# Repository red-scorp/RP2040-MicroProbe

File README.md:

```
 ___   ___  ___   ___     _   ___                          
| |_) | |_)  ) ) / / \ /_| | / / \                         
|_| \ |_|   /_/_ \_\_/   |_| \_\_/                         
 _      _   __    ___   ___   ___   ___   ___   ___   ____ 
| |\/| | | / /`  | |_) / / \ | |_) | |_) / / \ | |_) | |_  
|_|  | |_| \_\_, |_| \ \_\_/ |_|   |_| \ \_\_/ |_|_) |_|__ 
```

# RP2040-MicroProbe Project

The **RP2040-MicroProbe** project aims to create smaller version of RP2040-DebugProbe.

## RP2040-MicroProbe Board

The **RP2040-MicroProbe** board is a 4-layer design intended to accommodate the popular Raspberry Pi RP2040 MCU with all required component to function identically to Raspberry Pi Debug Probe.

This board features target JTAG connector and PC host micro-USB connector. It also has a SWD connector and UART connector for the main MCU debugging. The board is pin-compatible with Raspberry Pi Debug Probe and can be used with the same picoprobe SW.

Preview:

You can view the [Schematics in PDF format](doc/RP2040-MicroProbe.pdf) for detailed information.

STEP 3D file is available [with pins](doc/RP2040-MicroProbe.step).

Features:

- Very small form-factor of about 40x18mm.
- Raspberry Pi RP2040 MCU as a heart of the board.
- 2x5 1.27mm JTAG connector for programming and debugging.
- 1x8 2.54mm SWD/UART/Power connector for programming and debugging.
- Micro USB connector for power and communication.
- Several LEDs to indicate power and status.
- Castellated holes connector for main MCU debugging.
- BOOTSEL button to enter the bootloader mode for flashing new picoprobe SW.
- Pin-compatible with Raspberry Pi Debug Probe.
- Extra TARGET_RESET line connected to GPIO10 for target MCU reset over JTAG.
- Flat bottom side for easy mounting as a daughter board.

CAM files, as well as the BOM and CPL files for JLCPCB, are available.

## Version History

### v1.0b1

Initial release for testing purposes.

## Links

- [Raspberry Pi RP2040 information page](https://www.raspberrypi.com/documentation/microcontrollers/rp2040.html).
- [Raspberry Pi Debug Probe information page](https://www.raspberrypi.com/documentation/microcontrollers/debug-probe.html).
- [Picoprobe SW for the board](https://github.com/raspberrypi/picoprobe).

## How to Help

Your contributions as code, resources, or finances are welcome! Please contact me directly via email at andriy.golovnya@gmail.com or through my [GitHub profile](https://github.com/red-scorp).

If you'd like to make a financial contribution, you can donate via [PayPal](http://paypal.me/redscorp) or [Ko-Fi](http://ko-fi.com/redscorp). Your support is greatly appreciated.

Thanks in advance!

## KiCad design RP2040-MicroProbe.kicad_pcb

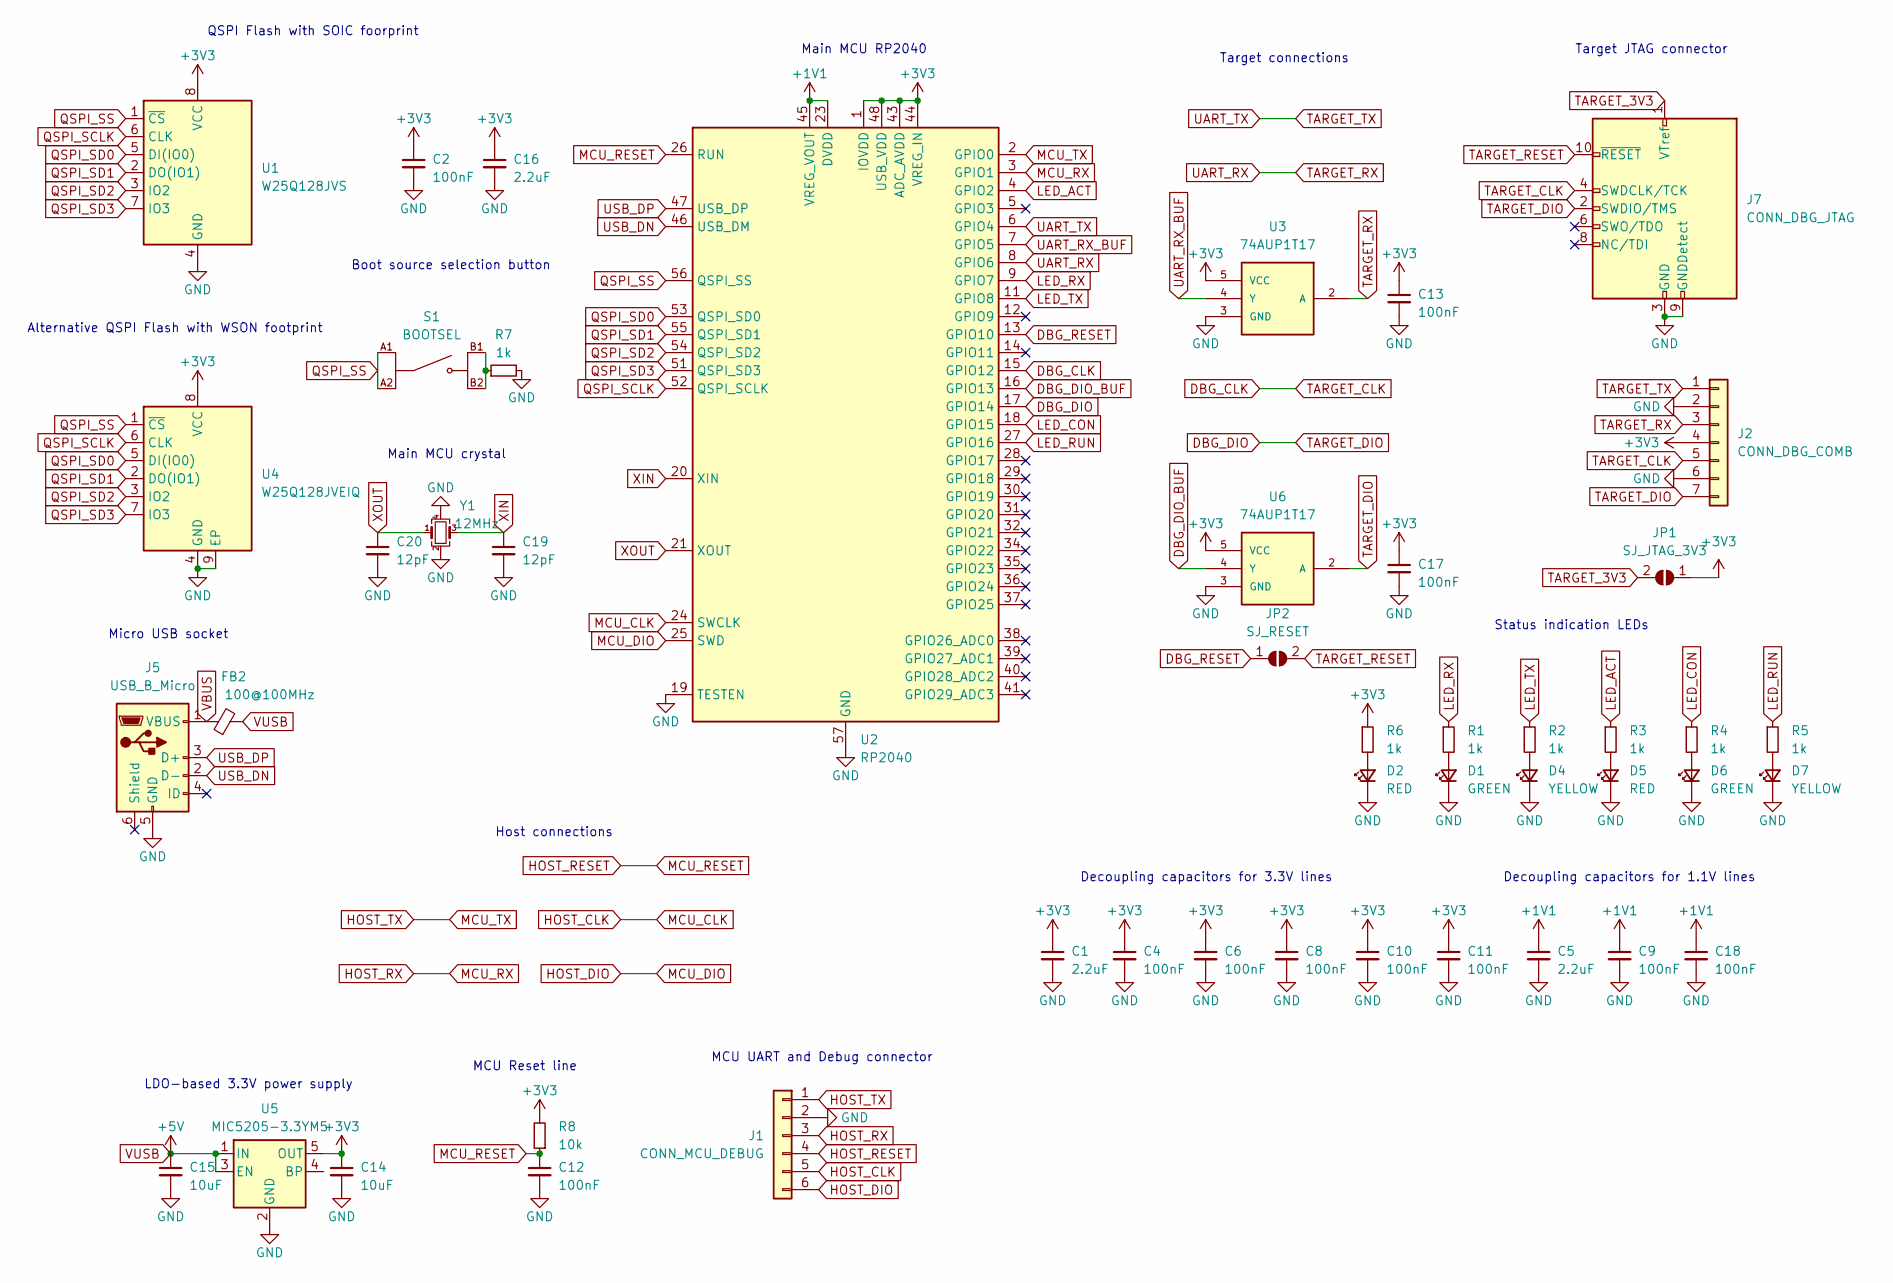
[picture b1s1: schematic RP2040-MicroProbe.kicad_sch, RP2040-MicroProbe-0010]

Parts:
C1, C5, C16: 2.2uF; C_0603_1608Metric
C2, C4, C6, C8, C9, C10, C11, C12, C13, C17, C18: 100nF; C_0402_1005Metric
C14, C15: 10uF; C_0805_2012Metric
C19, C20: 12pF; C_0402_1005Metric
D1, D6: GREEN; LED_0603_1608Metric
D2, D5: RED; LED_0603_1608Metric
D4, D7: YELLOW; LED_0603_1608Metric
FB2: 100@100MHz; L_0805_2012Metric
J1: CONN_MCU_DEBUG; PinHeader_1x06_P2.54mm_Vertical
J2: CONN_DBG_COMB; PinSocket_1x07_P2.54mm_Vertical
J5: USB_B_Micro; USB_Micro-B_Molex_47346-0001
J7: CONN_DBG_JTAG; PinHeader_2x05_P1.27mm_Vertical_SMD
JP1: SJ_JTAG_3V3; SolderJumper-2_P1.3mm_Open_TrianglePad1.0x1.5mm
JP2: SJ_RESET; SolderJumper-2_P1.3mm_Open_TrianglePad1.0x1.5mm
R1, R2, R3, R4, R5, R6, R7: 1k; R_0402_1005Metric
R8: 10k; R_0402_1005Metric
S1: BOOTSEL; SW_EVPBB0AAB000; DIGI-KEY_PART_NUMBER P19888CT-ND
U1: W25Q128JVS; SOIC-8_5.23x5.23mm_P1.27mm
U2: RP2040; QFN-56-1EP_7x7mm_P0.4mm_EP3.2x3.2mm
U3, U6: 74AUP1T17; SOT-353_SC-70-5
U4: W25Q128JVEIQ; WSON-8-1EP_6x5mm_P1.27mm_EP3.4x4.3mm
U5: MIC5205-3.3YM5; SOT-23-5
Y1: 12MHz; Crystal_SMD_3225-4Pin_3.2x2.5mm

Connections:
+1V1: C5.1, C9.1, C18.1, U2.23 (DVDD), U2.45 (VREG_VOUT), U2.50 (DVDD)
+3V3: C1.1, C2.1, C4.1, C6.1, C8.1, C10.1, C11.1, C13.1, C14.1, C16.1, C17.1, J2.4, JP1.1 (A), R6.1, R8.2, U1.8 (VCC), U2.1 (IOVDD), U2.10 (IOVDD), U2.22 (IOVDD), U2.33 (IOVDD), U2.42 (IOVDD), U2.43 (ADC_AVDD), U2.44 (VREG_IN), U2.48 (USB_VDD), U2.49 (IOVDD), U3.5 (VCC), U4.8 (VCC), U5.5 (OUT), U6.5 (VCC)
DBG_CLK: J2.5, J7.4 (SWDCLK/TCK), U2.15 (GPIO12)
DBG_DIO: J2.7, J7.2 (SWDIO/TMS), U2.17 (GPIO14), U6.2 (A)
DBG_DIO_BUF: U2.16 (GPIO13), U6.4 (Y)
DBG_RESET: JP2.1 (A), U2.13 (GPIO10)
GND: C1.2, C2.2, C4.2, C5.2, C6.2, C8.2, C9.2, C10.2, C11.2, C12.2, C13.2, C14.2, C15.2, C16.2, C17.2, C18.2, C19.2, C20.2, D1.1 (K), D2.1 (K), D4.1 (K), D5.1 (K), D6.1 (K), D7.1 (K), J1.2, J2.2, J2.6, J5.5 (GND), J7.3 (GND), J7.5 (GND), J7.9 (GNDDetect), R7.2, U1.4 (GND), U2.19 (TESTEN), U2.57 (GND), U3.3 (GND), U4.4 (GND), U4.9 (EP), U5.2 (GND), U6.3 (GND), Y1.2, Y1.4
HOST_CLK: J1.5, U2.24 (SWCLK)
HOST_DIO: J1.6, U2.25 (SWD)
HOST_RESET: C12.1, J1.4, R8.1, U2.26 (RUN)
HOST_RX: J1.3, U2.3 (GPIO1)
HOST_TX: J1.1, U2.2 (GPIO0)
LED_ACT: R3.1, U2.4 (GPIO2)
LED_CON: R4.1, U2.18 (GPIO15)
LED_RUN: R5.1, U2.27 (GPIO16)
LED_RX: R1.1, U2.9 (GPIO7)
LED_TX: R2.1, U2.11 (GPIO8)
unnamed: D1.2 (A), R1.2
unnamed: D2.2 (A), R6.2
unnamed: D4.2 (A), R2.2
unnamed: D5.2 (A), R3.2
unnamed: D6.2 (A), R4.2
unnamed: D7.2 (A), R5.2
unnamed: R7.1, S1.B1, S1.B2
QSPI_SCLK: U1.6 (CLK), U2.52 (QSPI_SCLK), U4.6 (CLK)
QSPI_SD0: U1.5 (DI(IO0)), U2.53 (QSPI_SD0), U4.5 (DI(IO0))
QSPI_SD1: U1.2 (DO(IO1)), U2.55 (QSPI_SD1), U4.2 (DO(IO1))
QSPI_SD2: U1.3 (IO2), U2.54 (QSPI_SD2), U4.3 (IO2)
QSPI_SD3: U1.7 (IO3), U2.51 (QSPI_SD3), U4.7 (IO3)
QSPI_SS: S1.A1, S1.A2, U1.1 (~CS), U2.56 (QSPI_SS), U4.1 (~CS)
TARGET_3V3: J7.1 (VTref), JP1.2 (B)
TARGET_RESET: J7.10 (~RESET), JP2.2 (B)
TARGET_RX: J2.3, U2.8 (GPIO6), U3.2 (A)
TARGET_TX: J2.1, U2.6 (GPIO4)
UART_RX_BUF: U2.7 (GPIO5), U3.4 (Y)
USB_DN: J5.2 (D-), U2.46 (USB_DM)
USB_DP: J5.3 (D+), U2.47 (USB_DP)
VBUS: FB2.1, J5.1 (VBUS)
VUSB: C15.1, FB2.2, U5.1 (IN), U5.3 (EN)
XIN: C19.1, U2.20 (XIN), Y1.3
XOUT: C20.1, U2.21 (XOUT), Y1.1

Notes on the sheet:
Alternative QSPI Flash with WSON footprint
Main MCU RP2040
Status indication LEDs
Decoupling capacitors for 3.3V lines
Main MCU crystal
Decoupling capacitors for 1.1V lines
Target connections
Target JTAG connector
Micro USB socket
Host connections
MCU UART and Debug connector
Boot source selection button
LDO-based 3.3V power supply
MCU Reset line
QSPI Flash with SOIC foorprint

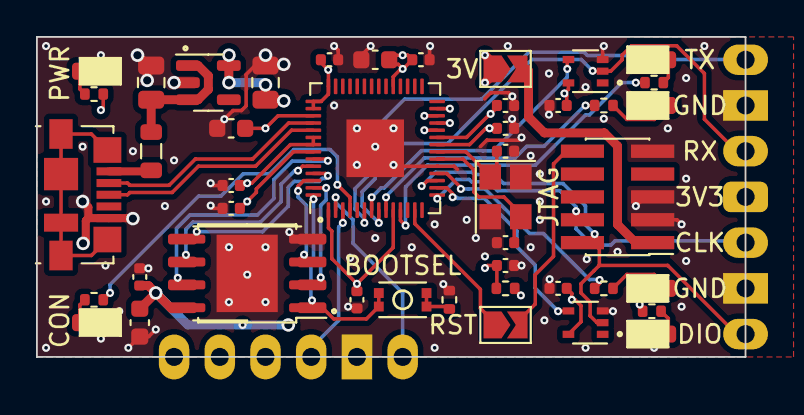
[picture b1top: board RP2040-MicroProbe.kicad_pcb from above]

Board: 4 copper layers, 39.4 x 17.8 mm, 47 parts (0 on the bottom side), 41 nets.

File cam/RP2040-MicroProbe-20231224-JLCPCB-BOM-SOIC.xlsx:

Qty | Designator | Footprint | JLCPCB Part# | Comment
2 | D7,D4 | 0603 | C72038 | YELLOW
11 | C4,C11,C9,C17,C12,C13,C18,C2,C6,C10,C8 | 0402 | C1525 | 100nF
3 | C5,C1,C16 | 0603 | C1604 | 2.2uF
1 | FB2 | 0805 | C1015 | GZ2012D101TF
2 | U3,U6 | SC-70-5 | C2652100 | 74AUP1T17
2 | D2,D5 | 0603 | C2286 | RED
1 | J5 | SMD | C2763165 | USB B micro
2 | C20,C19 | 0402 | C1547 | 12pF
1 | U2 | LQFN-56(7x7) | C2040 | RP2040
7 | R3,R7,R5,R1,R6,R4,R2 | 0402 | C11702 | 1k
2 | C14,C15 | 0805 | C15850 | 10uF
1 | J7 | SMD,P=1.27mm | C598540 | JTAG
1 | S1 | SMD,1.6x2.6mm | C913786 | 1TS026A-1800-0553-CT
2 | D1,D6 | 0603 | C72043 | GREEN
1 | Y1 | SMD3225-4P | C9002 | 12MHz
1 | U1 | SOIC-8-208mil | C97521 | W25Q128JVS
1 | U5 | SOT-23-5 | C37970 | MIC5205-3.3YM5
1 | R8 | 0402 | C25744 | 10k

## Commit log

2023-12-18 Added initial design based on RP2040-DebugProbe board
2023-12-18 Cleanup components a bit. Changed few components and footprints.
2023-12-18 Moved stuff around
2023-12-19 Added traces and vias
2023-12-24 Rotated JTAG connector. Moved stuff around
2023-12-25 Added README.md
2023-12-25 Generated CAM files
2023-12-25 Generated PNG preview
2023-12-25 Generated 3D file
2023-12-25 Generated PDF schematics
2023-12-26 Added basic BOM and CPL
2023-12-26 Generated BOM and CPL files
2024-01-08 Fixes a typo in schematics

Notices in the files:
RP2040-MicroProbe.kicad_pcb:
(c) 2023-2024 Andriy Golovnya
